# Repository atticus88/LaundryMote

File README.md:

LaundryMote
===========

####Base Line Utility Usage

Attach moteino to usb, and get the name of the device.  Edit the path to the device in server.js

```js
...
var serial = new serialport.SerialPort("/dev/tty.usbserial-A603BSK3", { baudrate : 115200, parser: serialport.parsers.readline("\n") });
...
```

Start the server

```
server@server$ node server.js
```

If the server errors out try starting it again somtimes the `LaundryMote: 915 Mhz....` will cause the server to stop.

Browse to http://localhost:3030/

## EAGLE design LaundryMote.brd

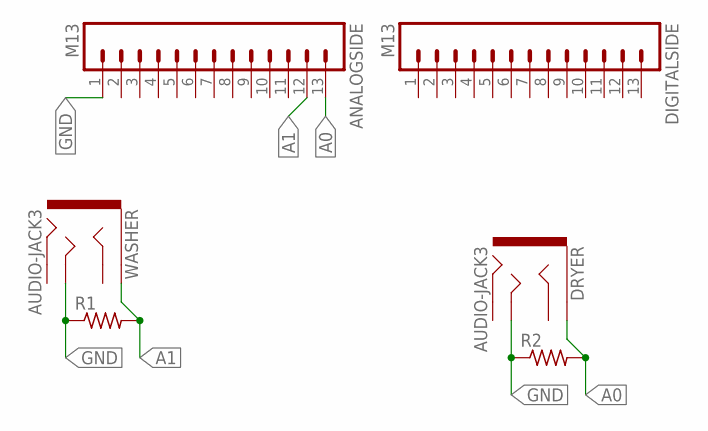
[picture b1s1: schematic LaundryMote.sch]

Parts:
ANALOGSIDE: M13; 1X13
DIGITALSIDE: M13; 1X13
DRYER: AUDIO-JACK3; AUDIO-JACK-TRRS-SMD
R1, R2: R-US_0207/7; 0207/7
WASHER: AUDIO-JACK3; AUDIO-JACK-TRRS-SMD

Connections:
A0: ANALOGSIDE.13, DRYER.EARTH, R2.2
A1: ANALOGSIDE.12, R1.2, WASHER.EARTH
GND: ANALOGSIDE.1, DRYER.TIP, R1.1, R2.1, WASHER.TIP

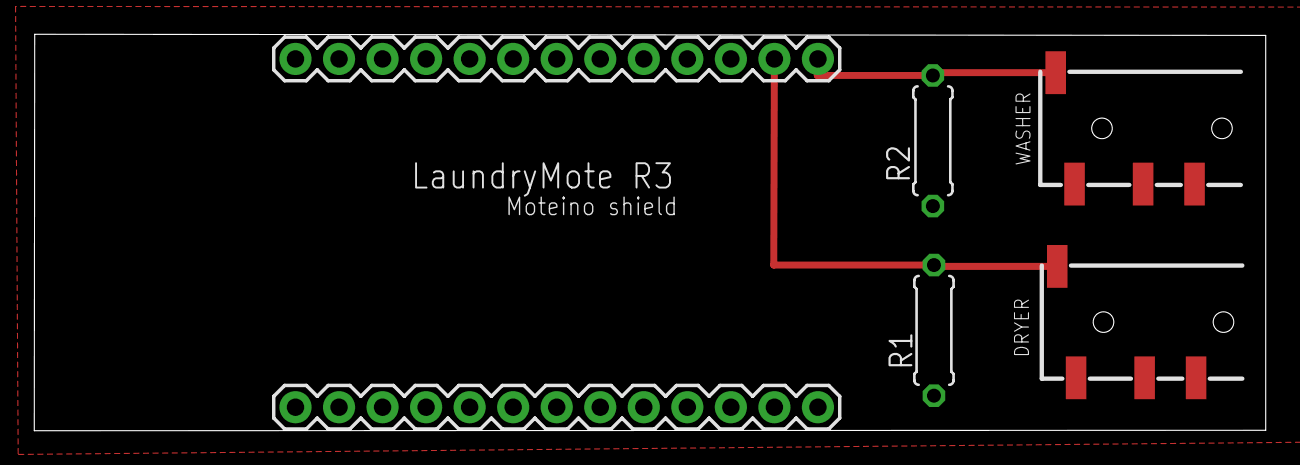
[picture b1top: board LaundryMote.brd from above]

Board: 2 copper layers, 71.8 x 23.1 mm, 7 parts (0 on the bottom side), 3 nets.

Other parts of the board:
E$1: OSHWLOGO_TOL_0.2

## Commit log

2014-02-12 LaundryMote R3 started, NodeJS baseline utility
2014-02-12 NodeJS baseline utility
2014-02-12 rename folder and clear database
2014-02-12 added debug/graph json output

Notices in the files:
parts and their libraries:
SparkFun-Connectors: Licensing: CC v3.0 Share-Alike You are welcome to use this library for commercial purposes.
